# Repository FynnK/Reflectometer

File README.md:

---
tags:
  - electronics
  - hardware-design
  - water-sensor
  - obsidian-skills
status: design-complete
---

---
tags:
  - electronics
  - hardware-design
  - water-sensor
status: design-complete
---

# Multi-LED Spectral Water Quality Sensor

> [!info] Project Overview
> A 24-bit isolated sensing system using pulsed 100mA current sources to measure liquid reflection across three wavelengths (Red, Green, Blue).

## System Architecture

```mermaid
graph TD
    %% -- Non-Isolated Side --
    subgraph NonIsolated ["Power and Control (Digital)"]
        USB[MicroUSB Connector]
        ESP32[ESP32-C3 MCU]
        C_IN[10uF CL21A106]
    end

    %% -- Isolation Barrier --
    subgraph Moat ["Isolation Barrier"]
        ISO1[ISO6742 SPI]
        ISO2[ISO6742 Control]
        ISO3[ISO6742 Extra]
        TRACO[TEA 1-0505 DC/DC]
    end

    %% -- Isolated Side --
    subgraph Isolated ["Isolated Analog Island"]
        %% Power Path
        L47[47uH WE Inductor]
        C_BULK[10uF Filtered]
        TPS[TPS60403 Inverter]
        
        %% Control Signals
        PWM[PWM Filter]
        GATE_SEL[BS170 Selector Gates]
        
        %% Signal Chain
        PD[BPW34S Photodiode]
        TIA[TLV172 TIA]
        ADC[ADS131M02]
        
        %% LED Current Path
        LEDS[RGB LED Array]
        SINK[BS170 Regulator]
        RSENSE[10 ohm Sense Resistor]
    end

    %% Cross-Barrier Links
    USB --> C_IN
    C_IN --> ESP32
    C_IN --> TRACO
    ESP32 --> ISO1
    ESP32 --> ISO2
    
    %% Isolated Routing
    TRACO --> L47
    L47 --> C_BULK
    C_BULK --> TPS
    C_BULK --> LEDS
    
    ISO1 --> ADC
    ISO2 --> PWM
    ISO2 --> GATE_SEL
    
    LEDS --> GATE_SEL
    GATE_SEL --> SINK
    SINK --> RSENSE
    RSENSE --> ADC
    
    PD --> TIA
    TIA --> ADC
````

## Hardware Component Logic

### 1. Power & Noise Suppression

- **Isolated DC/DC:** Uses the [[TEA 1-0505]] to break ground loops.
    
- **The Filter:** A Pi-filter using the **47uH Würth Inductor** and **Ferrite Beads** to scrub switching noise.
    
- **Negative Rail:** The **TPS60403** provides a -5V rail for the **TLV172** to allow the TIA to swing to absolute zero.

### 2. The 100mA Pulsed Source

> [!tip] Ratiometric Measurement
> 
> By routing the voltage from the **10 ohm Sense Resistor** back to ADC Channel 2, we calculate the ratio of reflected light to actual LED current. This cancels out power supply ripples.

- **Regulation:** TLV172 + BS170 (Main Sink).
    
- **Switching:** 3x BS170 (Color Selectors).

## Component List & Budget

|**Component**|**Function**|**Cost**|
|---|---|---|
|[[ADS131M02]]|24-bit ADC|€4.41|
|[[ISO6742]] (x3)|Digital Isolation|€7.68|
|[[TLV172]] (x2)|TIA & Current Source|€2.96|
|[[TEA 1-0505]]|Isolated Power|€1.65|

**Total Estimated BOM:** €24.64 ^total-cost

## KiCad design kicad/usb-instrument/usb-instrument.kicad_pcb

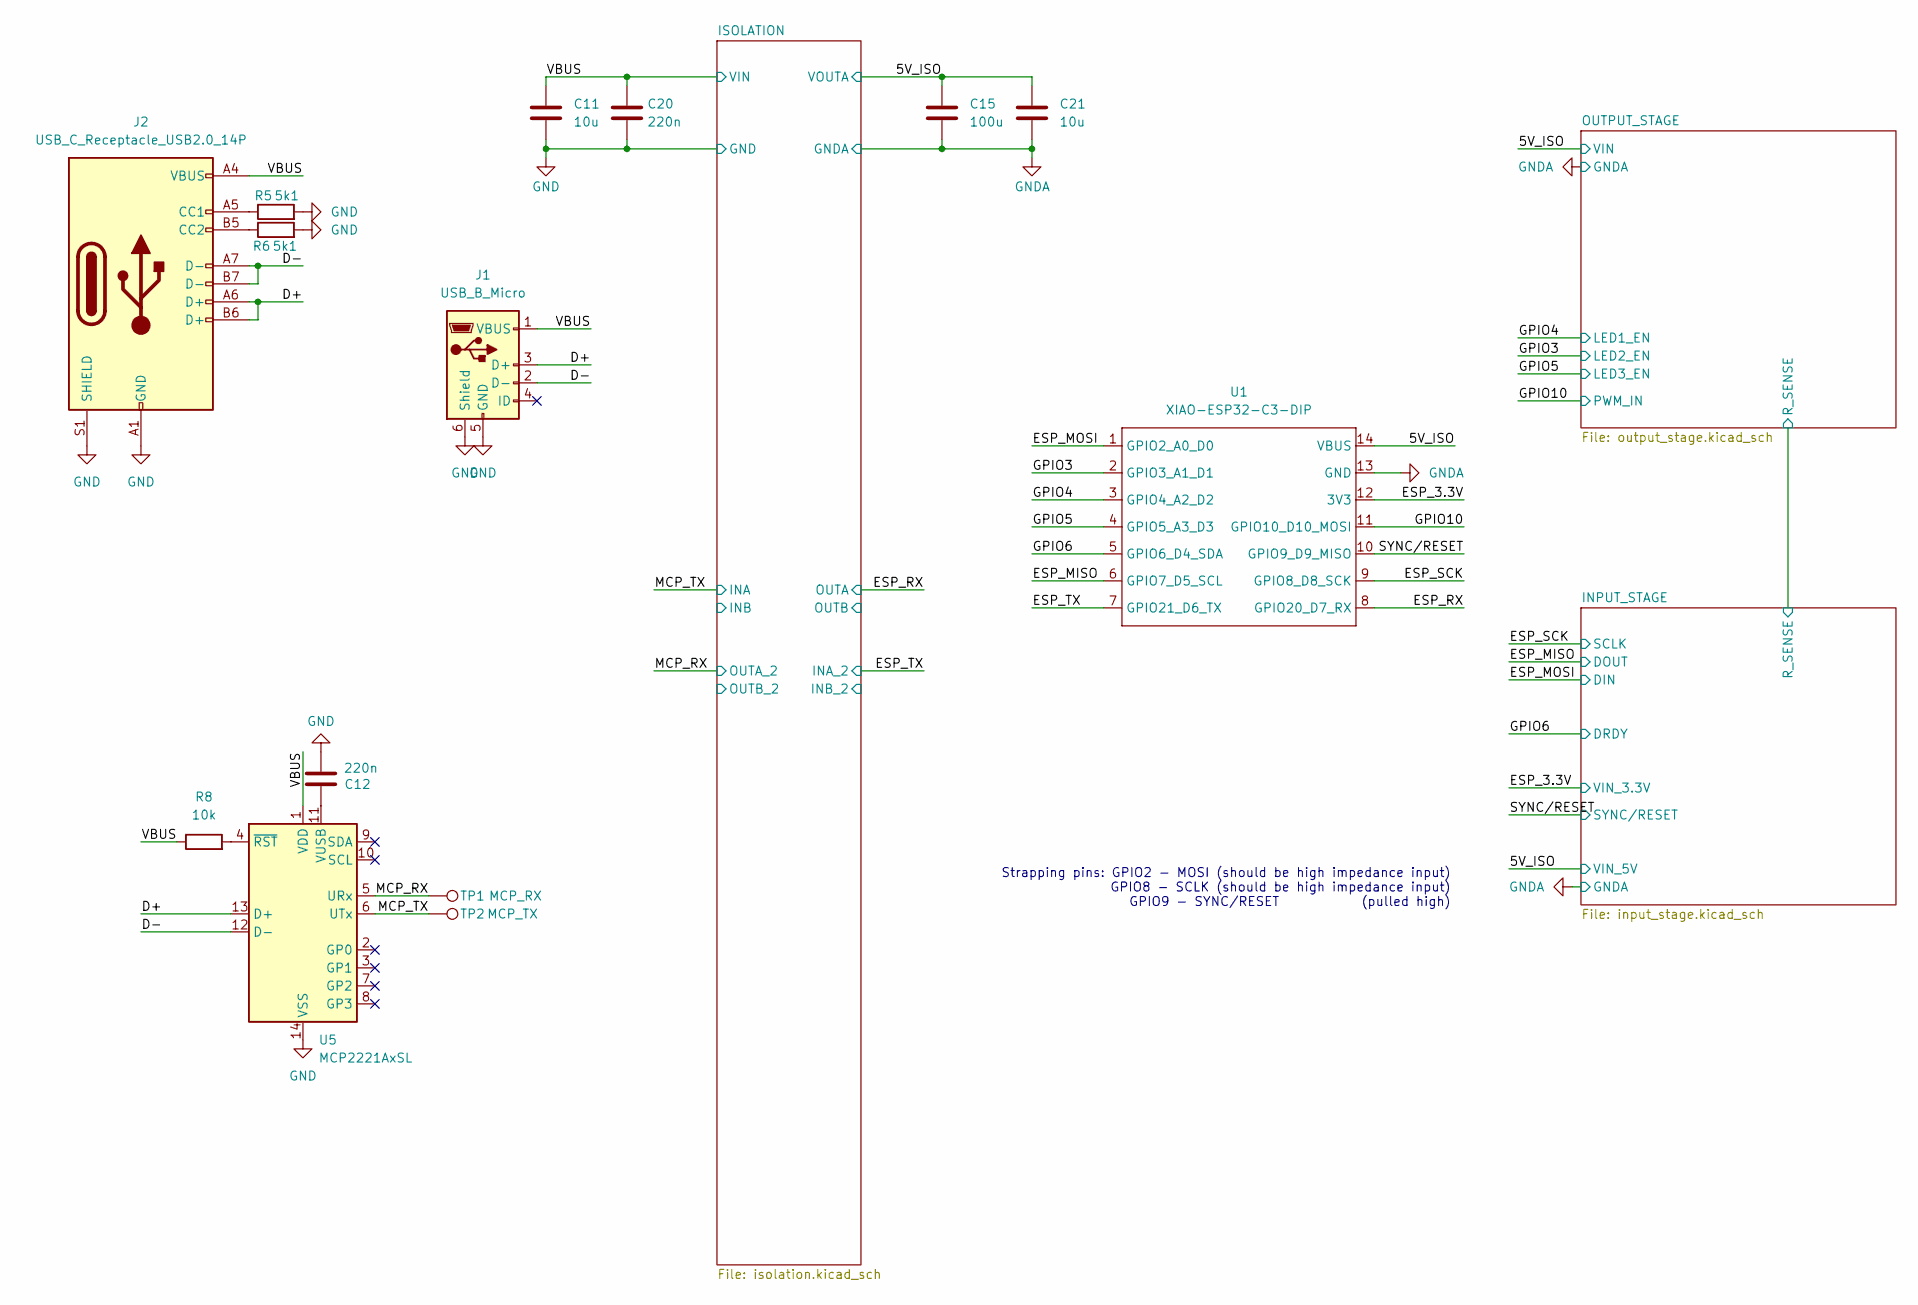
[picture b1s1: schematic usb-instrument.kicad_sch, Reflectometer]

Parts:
C11, C21: 10u; C_0805_2012Metric_Pad1.18x1.45mm_HandSolder
C12, C20: 220n; C_0805_2012Metric_Pad1.18x1.45mm_HandSolder
C15: 100u; CP_Elec_6.3x5.7
J1: USB_B_Micro; USB_Micro-B_Amphenol_10103594-0001LF_Horizontal
J2: USB_C_Receptacle_USB2.0_14P; USB_C_Receptacle_G-Switch_GT-USB-7010ASV
R5, R6: 5k1; R_0805_2012Metric_Pad1.20x1.40mm_HandSolder
R8: 10k; R_0805_2012Metric_Pad1.20x1.40mm_HandSolder
TP1: MCP_RX; TestPoint_Pad_D2.5mm
TP2: MCP_TX; TestPoint_Pad_D2.5mm
U1: XIAO-ESP32-C3-DIP; XIAO-ESP32-C3-DIP-SMD
U5: MCP2221AxSL; SOIC-14_3.9x8.7mm_P1.27mm

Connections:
/D+: J1.3 (D+), J2.A6 (D+), J2.B6 (D+), U5.13 (D+)
/D-: J1.2 (D-), J2.A7 (D-), J2.B7 (D-), U5.12 (D-)
/ESP_3.3V: U1.12 (3V3); also elsewhere on the board
/ESP_MISO: U1.6 (GPIO7_D5_SCL); also elsewhere on the board
/ESP_MOSI: U1.1 (GPIO2_A0_D0); also elsewhere on the board
/ESP_RX: U1.8 (GPIO20_D7_RX); also elsewhere on the board
/ESP_SCK: U1.9 (GPIO8_D8_SCK); also elsewhere on the board
/ESP_TX: U1.7 (GPIO21_D6_TX); also elsewhere on the board
/GPIO3: U1.2 (GPIO3_A1_D1); also elsewhere on the board
/GPIO4: U1.3 (GPIO4_A2_D2); also elsewhere on the board
/GPIO5: U1.4 (GPIO5_A3_D3); also elsewhere on the board
/GPIO6: U1.5 (GPIO6_D4_SDA); also elsewhere on the board
/GPIO10: U1.11 (GPIO10_D10_MOSI); also elsewhere on the board
/MCP_RX: TP1.1 (1_1), U5.5 (URx); also elsewhere on the board
/MCP_TX: TP2.1 (1_1), U5.6 (UTx); also elsewhere on the board
/SYNC/RESET: U1.10 (GPIO9_D9_MISO); also elsewhere on the board
GND: C11.2, C12.2, C20.2, J1.5 (GND), J1.6 (Shield), J2.A1 (GND), J2.A12 (GND), J2.B1 (GND), J2.B12 (GND), J2.S1 (SHIELD), R5.2, R6.2, U5.14 (VSS); also elsewhere on the board
GNDA: C15.2, C21.2, U1.13 (GND); also elsewhere on the board
unnamed: J2.A5 (CC1), R5.1
unnamed: J2.B5 (CC2), R6.1
unnamed: C12.1, U5.11 (VUSB)
unnamed: R8.2, U5.4 (~RST)
VCC: C11.1, C20.1, J1.1 (VBUS), J2.A4 (VBUS), J2.A9 (VBUS), J2.B4 (VBUS), J2.B9 (VBUS), R8.1, U5.1 (VDD); also elsewhere on the board
VCCQ: C15.1, C21.1, U1.14 (VBUS); also elsewhere on the board

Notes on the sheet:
Strapping pins: GPIO2 - MOSI (should be high impedance input) GPIO8 - SCLK (should be high impedance input) GPIO9 - SYNC/RESET (pulled high)

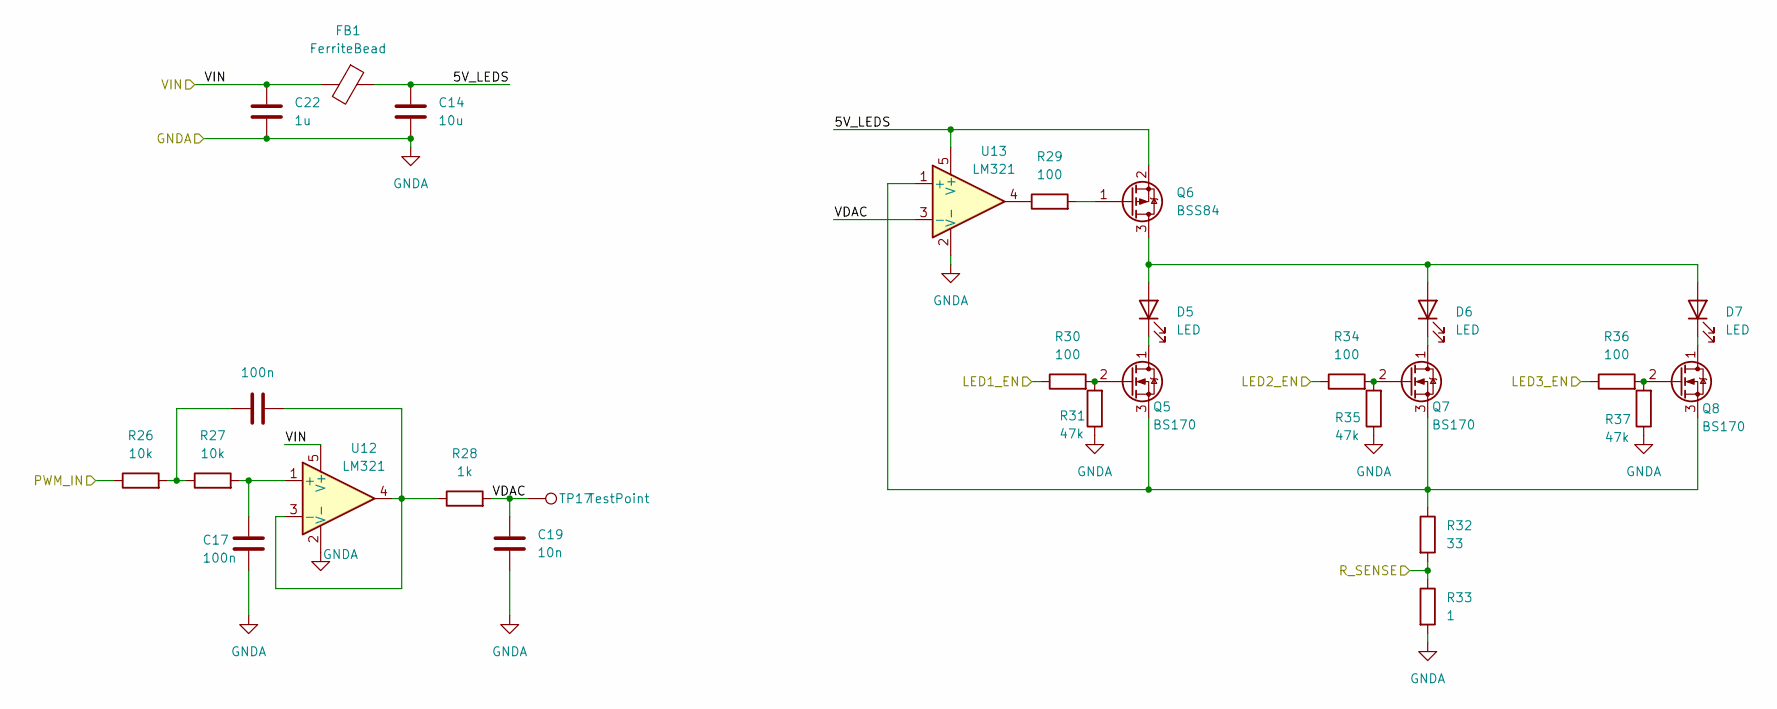
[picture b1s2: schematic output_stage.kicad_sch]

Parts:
C14: 10u; C_0805_2012Metric_Pad1.18x1.45mm_HandSolder
C17, C18: 100n; C_0805_2012Metric_Pad1.18x1.45mm_HandSolder
C19: 10n; C_0805_2012Metric_Pad1.18x1.45mm_HandSolder
C22: 1u; C_0805_2012Metric_Pad1.18x1.45mm_HandSolder
D5, D6, D7: LED; LED_1206_3216Metric
FB1: FerriteBead; L_0603_1608Metric_Pad1.05x0.95mm_HandSolder
Q5, Q7, Q8: BS170; SOT-23-3
Q6: BSS84; SOT-23
R26, R27: 10k; R_0805_2012Metric_Pad1.20x1.40mm_HandSolder
R28: 1k; R_0805_2012Metric_Pad1.20x1.40mm_HandSolder
R29, R30, R34, R36: 100; R_0805_2012Metric_Pad1.20x1.40mm_HandSolder
R31, R35, R37: 47k; R_0805_2012Metric_Pad1.20x1.40mm_HandSolder
R32: 33; R_0805_2012Metric_Pad1.20x1.40mm_HandSolder
R33: 1; R_0805_2012Metric_Pad1.20x1.40mm_HandSolder
TP17: TestPoint; TestPoint_Pad_D2.5mm
U12, U13: LM321; SOT-23-5

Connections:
/GPIO3: R34.1; also elsewhere on the board
/GPIO4: R30.1; also elsewhere on the board
/GPIO5: R36.1; also elsewhere on the board
/GPIO10: R26.1; also elsewhere on the board
/INPUT_STAGE/R_SENSE: R32.2, R33.1; also elsewhere on the board
/OUTPUT_STAGE/5V_LEDS: C14.1, FB1.1, Q6.2 (S), U13.5 (V+)
/OUTPUT_STAGE/VDAC: C19.1, R28.2, TP17.1 (1_1), U13.3 (-)
GNDA: C14.2, C17.1, C19.2, C22.2, R31.1, R33.2, R35.1, R37.1, U12.2 (V-), U13.2 (V-); also elsewhere on the board
unnamed: C18.1, R26.2, R27.1
unnamed: D5.2 (A), D6.2 (A), D7.2 (A), Q6.3 (D)
unnamed: D5.1 (K), Q5.1 (D)
unnamed: D6.1 (K), Q7.1 (D)
unnamed: D7.1 (K), Q8.1 (D)
unnamed: Q5.2 (G), R30.2, R31.2
unnamed: Q5.3 (S), Q7.3 (S), Q8.3 (S), R32.1, U13.1 (+)
unnamed: Q6.1 (G), R29.2
unnamed: Q7.2 (G), R34.2, R35.2
unnamed: Q8.2 (G), R36.2, R37.2
unnamed: R29.1, U13.4
unnamed: C17.2, R27.2, U12.1 (+)
unnamed: C18.2, R28.1, U12.3 (-), U12.4
VCCQ: C22.1, FB1.2, U12.5 (V+); also elsewhere on the board

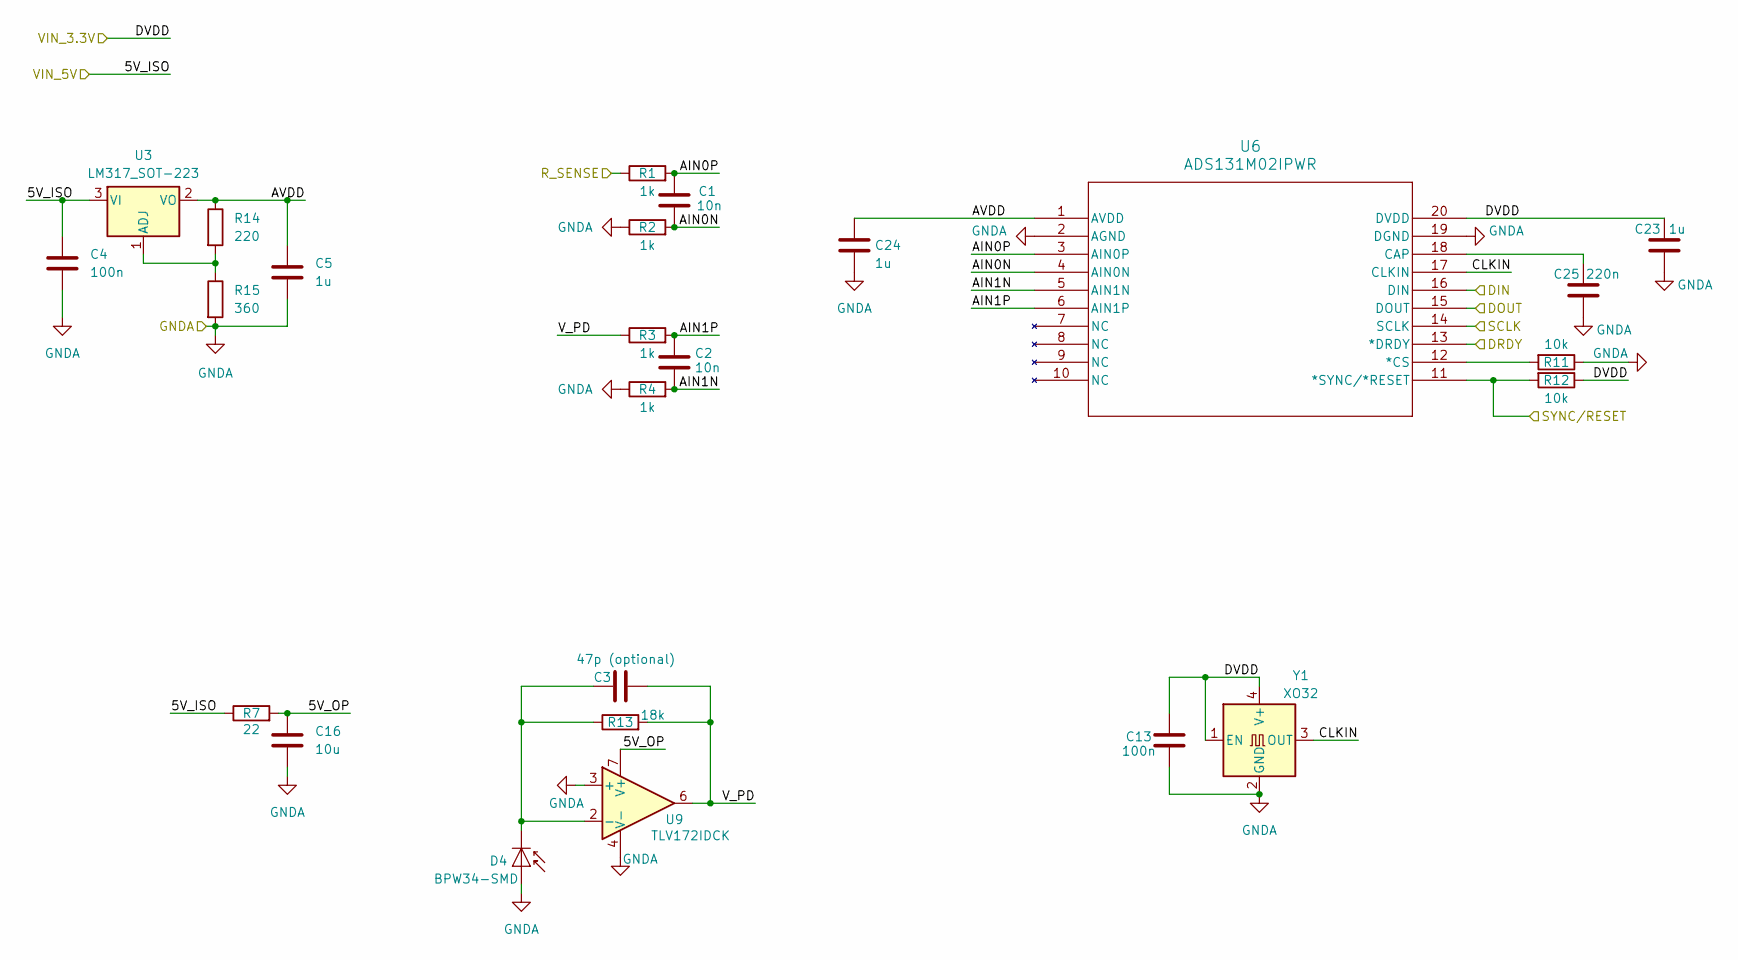
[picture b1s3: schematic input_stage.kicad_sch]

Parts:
C1, C2: 10n; C_0805_2012Metric_Pad1.18x1.45mm_HandSolder
C3: 47p (optional); C_0805_2012Metric_Pad1.18x1.45mm_HandSolder
C4, C13: 100n; C_0805_2012Metric_Pad1.18x1.45mm_HandSolder
C5, C23, C24: 1u; C_0805_2012Metric_Pad1.18x1.45mm_HandSolder
C16: 10u; C_0805_2012Metric_Pad1.18x1.45mm_HandSolder
C25: 220n; C_0805_2012Metric_Pad1.18x1.45mm_HandSolder
D4: BPW34-SMD; Osram_BPW34S-SMD
R1, R2, R3, R4: 1k; R_0805_2012Metric_Pad1.20x1.40mm_HandSolder
R7: 22; R_0805_2012Metric_Pad1.20x1.40mm_HandSolder
R11, R12: 10k; R_0805_2012Metric_Pad1.20x1.40mm_HandSolder
R13: 18k; R_0805_2012Metric_Pad1.20x1.40mm_HandSolder
R14: 220; R_0805_2012Metric_Pad1.20x1.40mm_HandSolder
R15: 360; R_0805_2012Metric_Pad1.20x1.40mm_HandSolder
U3: LM317_SOT-223; SOT-223-3_TabPin2
U6: ADS131M02IPWR; TSSOP20_PW_TEX
U9: TLV172IDCK; SOIC-8-1EP_3.9x4.9mm_P1.27mm_EP2.514x3.2mm
Y1: XO32; Crystal_SMD_7050-4Pin_7.0x5.0mm

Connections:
/ESP_3.3V: C13.1, C23.1, R12.1, U6.20 (DVDD), Y1.1 (EN), Y1.4 (V+); also elsewhere on the board
/ESP_MISO: U6.15 (DOUT); also elsewhere on the board
/ESP_MOSI: U6.16 (DIN); also elsewhere on the board
/ESP_SCK: U6.14 (SCLK); also elsewhere on the board
/GPIO6: U6.13 (*DRDY); also elsewhere on the board
/INPUT_STAGE/5V_OP: C16.1, R7.2, U9.7 (V+)
/INPUT_STAGE/AIN0N: C1.2, R2.2, U6.4 (AIN0N)
/INPUT_STAGE/AIN0P: C1.1, R1.2, U6.3 (AIN0P)
/INPUT_STAGE/AIN1N: C2.2, R4.2, U6.5 (AIN1N)
/INPUT_STAGE/AIN1P: C2.1, R3.2, U6.6 (AIN1P)
/INPUT_STAGE/AVDD: C5.1, C24.1, R14.1, U3.2 (VO), U6.1 (AVDD)
/INPUT_STAGE/CLKIN: U6.17 (CLKIN), Y1.3 (OUT)
/INPUT_STAGE/R_SENSE: R1.1; also elsewhere on the board
/INPUT_STAGE/V_PD: C3.2, R3.1, R13.2, U9.6
/SYNC/RESET: R12.2, U6.11 (*SYNC/*RESET); also elsewhere on the board
GNDA: C4.2, C5.2, C13.2, C16.2, C23.2, C24.2, C25.2, D4.2 (A), R2.1, R4.1, R11.1, R15.2, U6.2 (AGND), U6.19 (DGND), U9.3 (+), U9.4 (V-), Y1.2 (GND); also elsewhere on the board
unnamed: C3.1, D4.1 (K), R13.1, U9.2 (-)
unnamed: R14.2, R15.1, U3.1 (ADJ)
unnamed: R11.2, U6.12 (*CS)
unnamed: C25.1, U6.18 (CAP)
VCCQ: C4.1, R7.1, U3.3 (VI); also elsewhere on the board

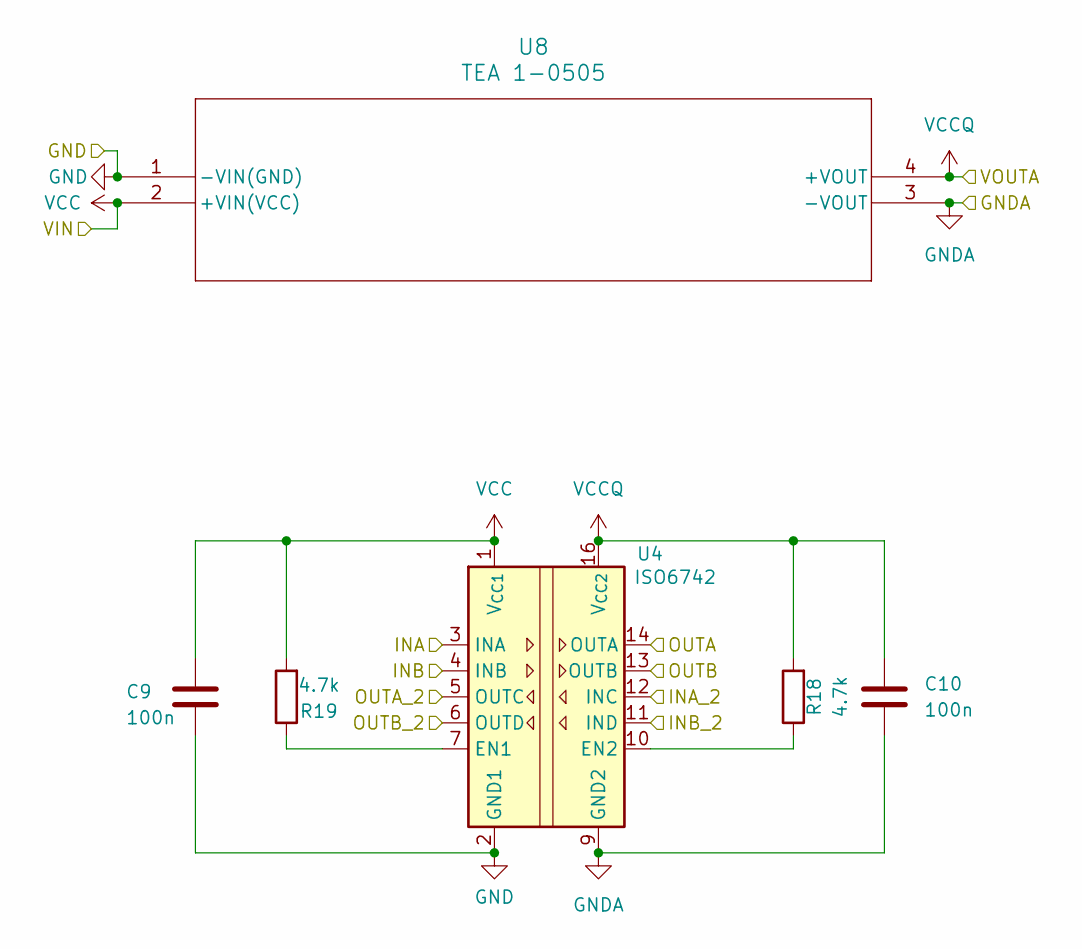
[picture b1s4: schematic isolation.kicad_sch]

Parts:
C9, C10: 100n; C_0805_2012Metric_Pad1.18x1.45mm_HandSolder
R18, R19: 4.7k; R_0805_2012Metric_Pad1.20x1.40mm_HandSolder
U4: ISO6742; SOIC-16W_7.5x10.3mm_P1.27mm
U8: TEA 1-0505; Converter_DCDC_TRACO_TEA1-xxxx_THT

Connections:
/ESP_RX: U4.14 (OUTA); also elsewhere on the board
/ESP_TX: U4.12 (INC); also elsewhere on the board
/ISOLATION/INB: U4.4 (INB)
/ISOLATION/INB_2: U4.11 (IND)
/ISOLATION/OUTB: U4.13 (OUTB)
/ISOLATION/OUTB_2: U4.6 (OUTD)
/MCP_RX: U4.5 (OUTC); also elsewhere on the board
/MCP_TX: U4.3 (INA); also elsewhere on the board
GND: C9.2, U4.2 (GND1), U4.8 (GND1), U8.1 (-VIN(GND)); also elsewhere on the board
GNDA: C10.2, U4.9 (GND2), U4.15 (GND2), U8.3 (-VOUT); also elsewhere on the board
unnamed: R19.1, U4.7 (EN1)
unnamed: R18.1, U4.10 (EN2)
VCC: C9.1, R19.2, U4.1 (V_{CC1}), U8.2 (+VIN(VCC)); also elsewhere on the board
VCCQ: C10.1, R18.2, U4.16 (V_{CC2}), U8.4 (+VOUT); also elsewhere on the board

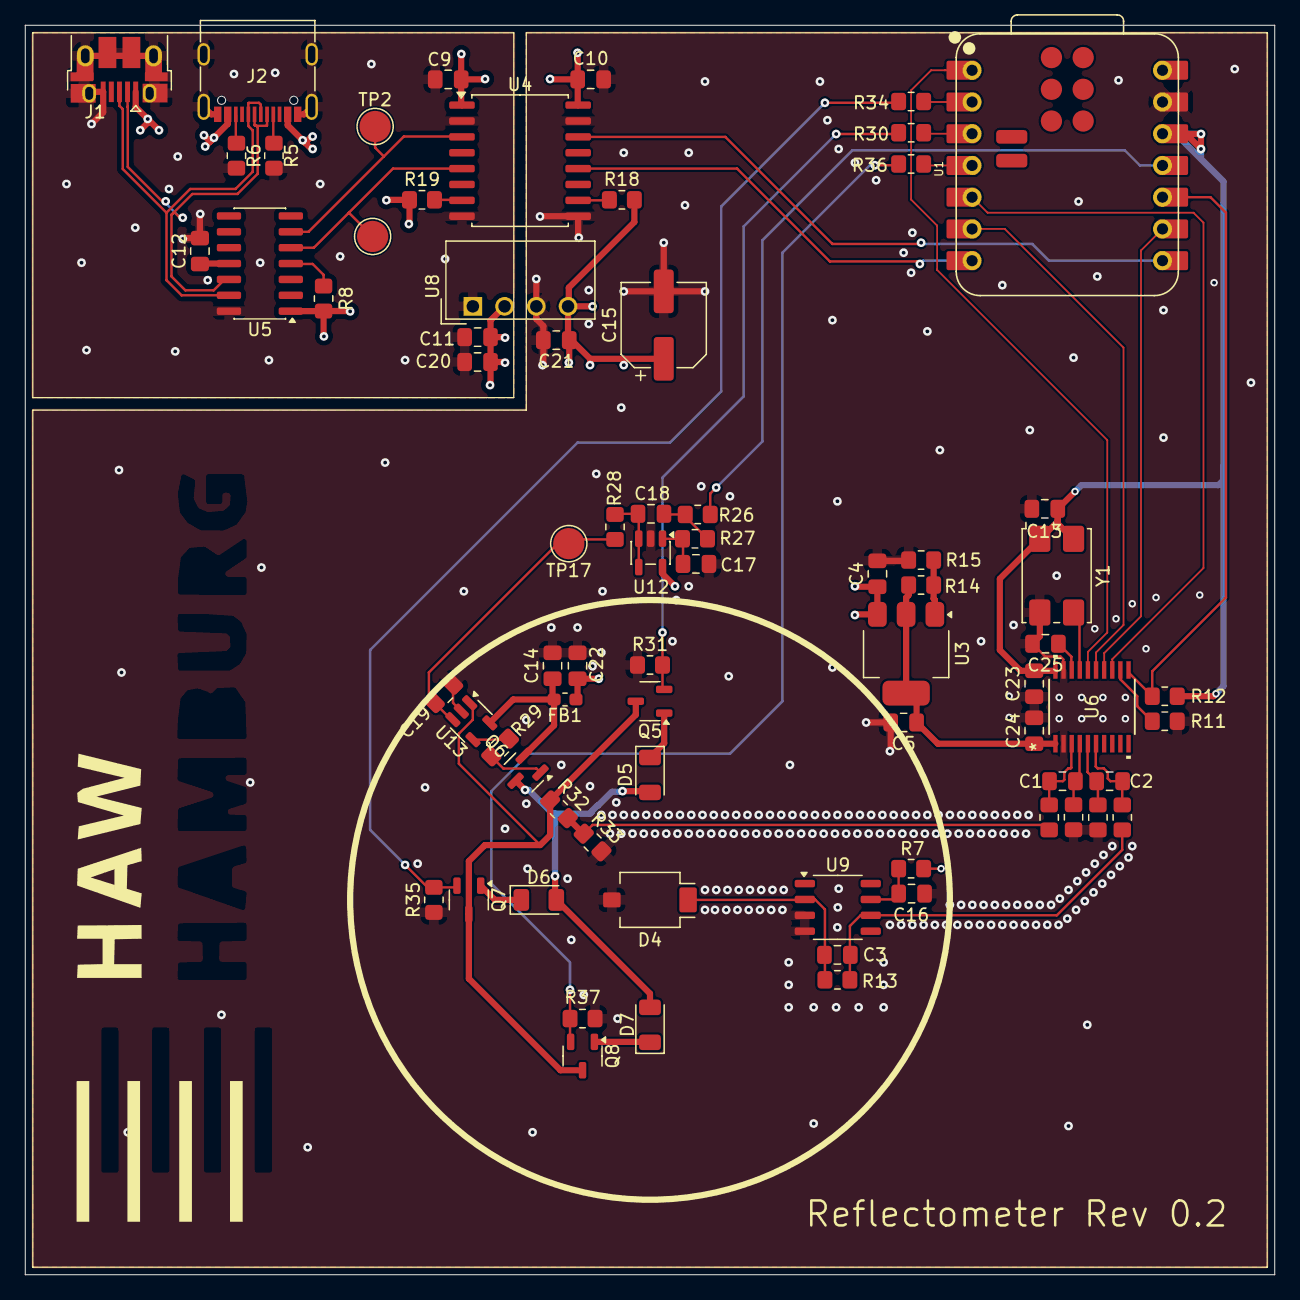
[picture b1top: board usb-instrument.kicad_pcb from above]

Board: 4 copper layers, 100.0 x 100.0 mm, 73 parts (0 on the bottom side), 54 nets.

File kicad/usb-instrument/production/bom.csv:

Designator,Footprint,Quantity,Value,LCSC Part #
"C1, C19, C2",0805,3,10n,
"C10, C13, C17, C18, C4, C9",0805,6,100n,
"C11, C14, C16, C21",0805,4,10u,
"C12, C20, C25",0805,3,220n,
C15,CP_Elec_6.3x5.7,1,100u,
"C22, C23, C24, C5",0805,4,1u,
C3,0805,1,47p (optional),
D4,Osram_BPW34S-SMD,1,BPW34-SMD,
"D5, D6, D7",1206,3,LED,
FB1,0603,1,FerriteBead,
J1,USB_Micro-B_Amphenol_10103594-0001LF_Horizontal,1,USB_B_Micro,
J2,USB_C_Receptacle_G-Switch_GT-USB-7010ASV,1,USB_C_Receptacle_USB2.0_14P,
"Q5, Q7, Q8",SOT-23-3,3,BS170,
Q6,SOT-23,1,BSS84,
"R1, R2, R28, R3, R4",0805,5,1k,
"R11, R12, R26, R27, R8",0805,5,10k,
R13,0805,1,18k,
R14,0805,1,220,
R15,0805,1,360,
"R18, R19",0805,2,4.7k,
"R29, R30, R34, R36",0805,4,100,
"R31, R35, R37",0805,3,47k,
R32,0805,1,33,
R33,0805,1,1,
"R5, R6",0805,2,5k1,
R7,0805,1,22,
TP1,TestPoint_Pad_D2.5mm,1,MCP_RX,
TP17,TestPoint_Pad_D2.5mm,1,TestPoint,
TP2,TestPoint_Pad_D2.5mm,1,MCP_TX,
U1,XIAO-ESP32-C3-DIP-SMD,1,XIAO-ESP32-C3-DIP,
"U12, U13",SOT-23-5,2,LM321,
U3,SOT-223-3_TabPin2,1,LM317_SOT-223,
U4,SOIC-16W_7.5x10.3mm_P1.27mm,1,ISO6742,
U5,SOIC-14_3.9x8.7mm_P1.27mm,1,MCP2221AxSL,
U6,TSSOP20_PW_TEX,1,ADS131M02IPWR,
U8,Converter_DCDC_TRACO_TEA1-xxxx_THT,1,TEA 1-0505,
U9,SOIC-8-1EP_3.9x4.9mm_P1.27mm_EP2.514x3.2mm,1,TLV172IDCK,
Y1,Crystal_SMD_7050-4Pin_7.0x5.0mm,1,XO32,

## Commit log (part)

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2026-05-03 begin layout
2026-05-08 geroutet
2026-05-08 vias + logo
2026-05-08 smal fixes
2026-05-08 added production files
2026-05-08 added Title & Rev
2026-05-08 silkscreen fix
2026-06-24 added reflectometer firmware?
2026-06-24 Revert "added reflectometer firmware?"
    This reverts commit 9538dd181f0abf5c2600e678e5beb3e59aa697ee.
2026-06-24 added reflectometer firmware
2026-06-27 Software for Reflectometer
2026-06-28 Ergänzung der LED Steuerung in der Software
2026-06-28 Added LED mA to plot
2026-06-29 updated footprints
